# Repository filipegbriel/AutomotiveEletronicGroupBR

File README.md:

# AutomotiveEletronicGroupBR
This is the gitdepository for the academic automotive eletronic group, composed mainly by FATEC and USP.

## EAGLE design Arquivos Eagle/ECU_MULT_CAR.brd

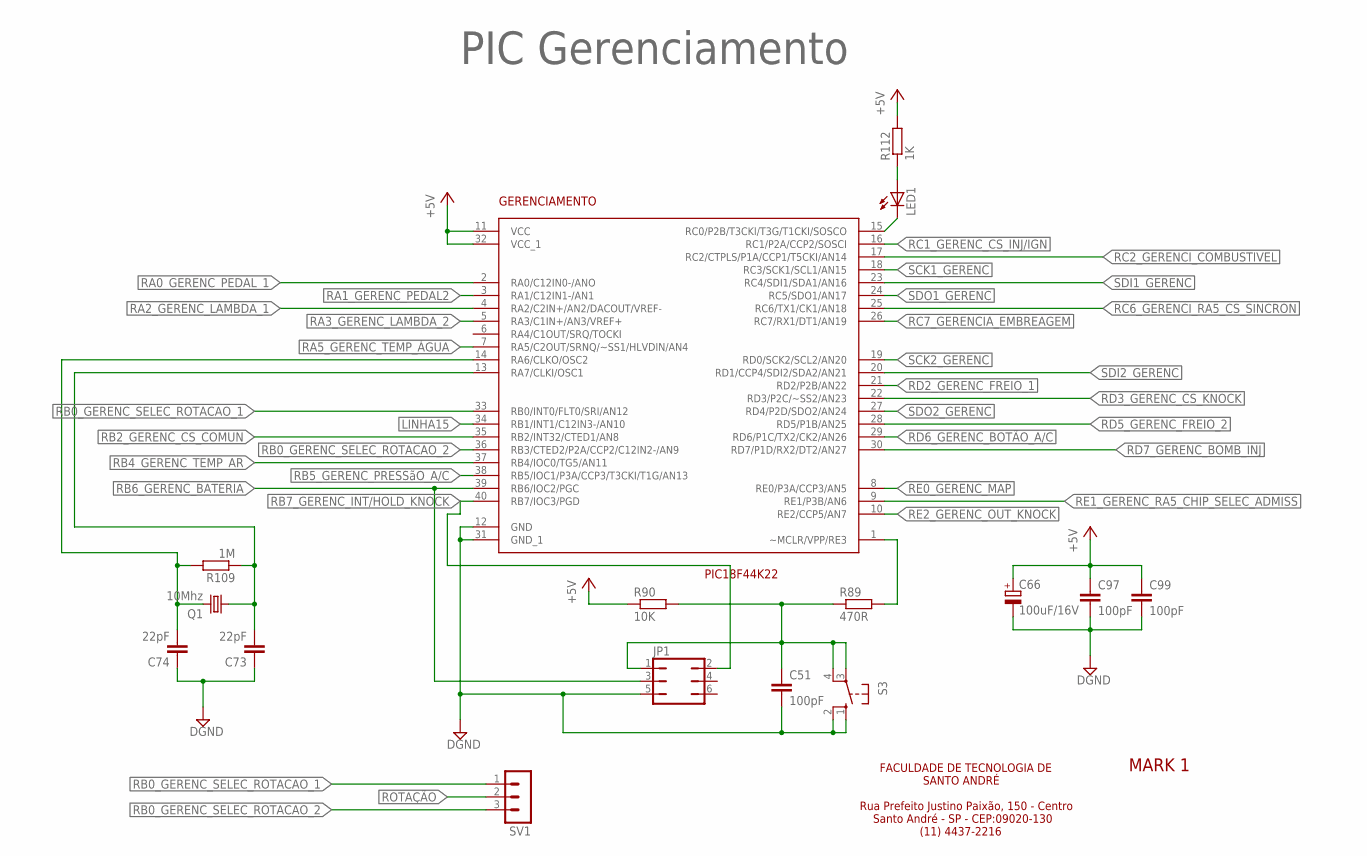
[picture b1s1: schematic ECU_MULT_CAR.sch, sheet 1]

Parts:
C51, C97, C99: 100pF; C0805
C66: 100uF/16V; E2,5-7
C73, C74: 22pF; C0805
GERENCIAMENTO: PIC18F44K22; DIP40
JP1: JP3Q
LED1: LEDKA-3528ASYC; KA-3528ASYC
Q1: 10Mhz; SM49
R89: 470R; M0805
R90: 10K; M0805
R109: 1M; M0805
R112: 1K; M0805
S3: 10-XX; B3F-10XX
SV1: MA03-1

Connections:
+5V: C66.+, C97.1, C99.1, GERENCIAMENTO.11 (VCC), GERENCIAMENTO.32 (VCC_1), R90.1, R112.2; also elsewhere on the board
DGND: C51.2, C66.-, C73.1, C74.1, C97.2, C99.2, GERENCIAMENTO.12 (GND), GERENCIAMENTO.31 (GND_1), JP1.5, S3.1 (S), S3.2 (S1); also elsewhere on the board
LINHA15: GERENCIAMENTO.34 (RB1/INT1/C12IN3-/AN10); also elsewhere on the board
unnamed: C73.2, GERENCIAMENTO.13 (RA7/CLKI/OSC1), Q1.1, R109.1
unnamed: GERENCIAMENTO.1 (~MCLR/VPP/RE3), R89.2
unnamed: C51.1, JP1.1, R89.1, R90.2, S3.3, S3.4 (P1)
unnamed: GERENCIAMENTO.15 (RC0/P2B/T3CKI/T3G/T1CKI/SOSCO), LED1.C
unnamed: LED1.A, R112.1
unnamed: C74.2, GERENCIAMENTO.14 (RA6/CLKO/OSC2), Q1.2, R109.2
RA0_GERENC_PEDAL_1: GERENCIAMENTO.2 (RA0/C12IN0-/ANO); also elsewhere on the board
RA1_GERENC_PEDAL2: GERENCIAMENTO.3 (RA1/C12IN1-/AN1); also elsewhere on the board
RA2_GERENC_LAMBDA_1: GERENCIAMENTO.4 (RA2/C2IN+/AN2/DACOUT/VREF-); also elsewhere on the board
RA3_GERENC_LAMBDA_2: GERENCIAMENTO.5 (RA3/C1IN+/AN3/VREF+); also elsewhere on the board
RA5_GERENC_TEMP_ÁGUA: GERENCIAMENTO.7 (RA5/C2OUT/SRNQ/~SS1/HLVDIN/AN4); also elsewhere on the board
RB0_GERENC_SELEC_ROTACAO_1: GERENCIAMENTO.33 (RB0/INT0/FLT0/SRI/AN12), SV1.1
RB0_GERENC_SELEC_ROTACAO_2: GERENCIAMENTO.36 (RB3/CTED2/P2A/CCP2/C12IN2-/AN9), SV1.3
RB2_GERENC_CS_COMUN: GERENCIAMENTO.35 (RB2/INT32/CTED1/AN8); also elsewhere on the board
RB4_GERENC_TEMP_AR: GERENCIAMENTO.37 (RB4/IOC0/TG5/AN11); also elsewhere on the board
RB5_GERENC_PRESSãO_A/C: GERENCIAMENTO.38 (RB5/IOC1/P3A/CCP3/T3CKI/T1G/AN13); also elsewhere on the board
RB6_GERENC_BATERIA: GERENCIAMENTO.39 (RB6/IOC2/PGC), JP1.3; also elsewhere on the board
RB7_GERENC_INT/HOLD_KNOCK: GERENCIAMENTO.40 (RB7/IOC3/PGD), JP1.2; also elsewhere on the board
RC1_GERENC_CS_INJ/IGN: GERENCIAMENTO.16 (RC1/P2A/CCP2/SOSCI); also elsewhere on the board
RC2_GERENCI_COMBUSTIVEL: GERENCIAMENTO.17 (RC2/CTPLS/P1A/CCP1/T5CKI/AN14); also elsewhere on the board
RC6_GERENCI_RA5_CS_SINCRON: GERENCIAMENTO.25 (RC6/TX1/CK1/AN18); also elsewhere on the board
RC7_GERENCIA_EMBREAGEM: GERENCIAMENTO.26 (RC7/RX1/DT1/AN19); also elsewhere on the board
RD2_GERENC_FREIO_1: GERENCIAMENTO.21 (RD2/P2B/AN22); also elsewhere on the board
RD3_GERENC_CS_KNOCK: GERENCIAMENTO.22 (RD3/P2C/~SS2/AN23); also elsewhere on the board
RD5_GERENC_FREIO_2: GERENCIAMENTO.28 (RD5/P1B/AN25); also elsewhere on the board
RD6_GERENC_BOTÃO_A/C: GERENCIAMENTO.29 (RD6/P1C/TX2/CK2/AN26); also elsewhere on the board
RD7_GERENC_BOMB_INJ: GERENCIAMENTO.30 (RD7/P1D/RX2/DT2/AN27); also elsewhere on the board
RE0_GERENC_MAP: GERENCIAMENTO.8 (RE0/P3A/CCP3/AN5); also elsewhere on the board
RE1_GERENC_RA5_CHIP_SELEC_ADMISS: GERENCIAMENTO.9 (RE1/P3B/AN6); also elsewhere on the board
RE2_GERENC_OUT_KNOCK: GERENCIAMENTO.10 (RE2/CCP5/AN7); also elsewhere on the board
ROTAÇÃO: SV1.2; also elsewhere on the board
SCK1_GERENC: GERENCIAMENTO.18 (RC3/SCK1/SCL1/AN15); also elsewhere on the board
SCK2_GERENC: GERENCIAMENTO.19 (RD0/SCK2/SCL2/AN20); also elsewhere on the board
SDI1_GERENC: GERENCIAMENTO.23 (RC4/SDI1/SDA1/AN16); also elsewhere on the board
SDI2_GERENC: GERENCIAMENTO.20 (RD1/CCP4/SDI2/SDA2/AN21); also elsewhere on the board
SDO1_GERENC: GERENCIAMENTO.24 (RC5/SDO1/AN17); also elsewhere on the board
SDO2_GERENC: GERENCIAMENTO.27 (RD4/P2D/SDO2/AN24); also elsewhere on the board

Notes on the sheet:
PIC Gerenciamento
FACULDADE DE TECNOLOGIA DE SANTO ANDRÉ Rua Prefeito Justino Paixão, 150 - Centro Santo André - SP - CEP:09020-130 (11) 4437-2216
MARK 1

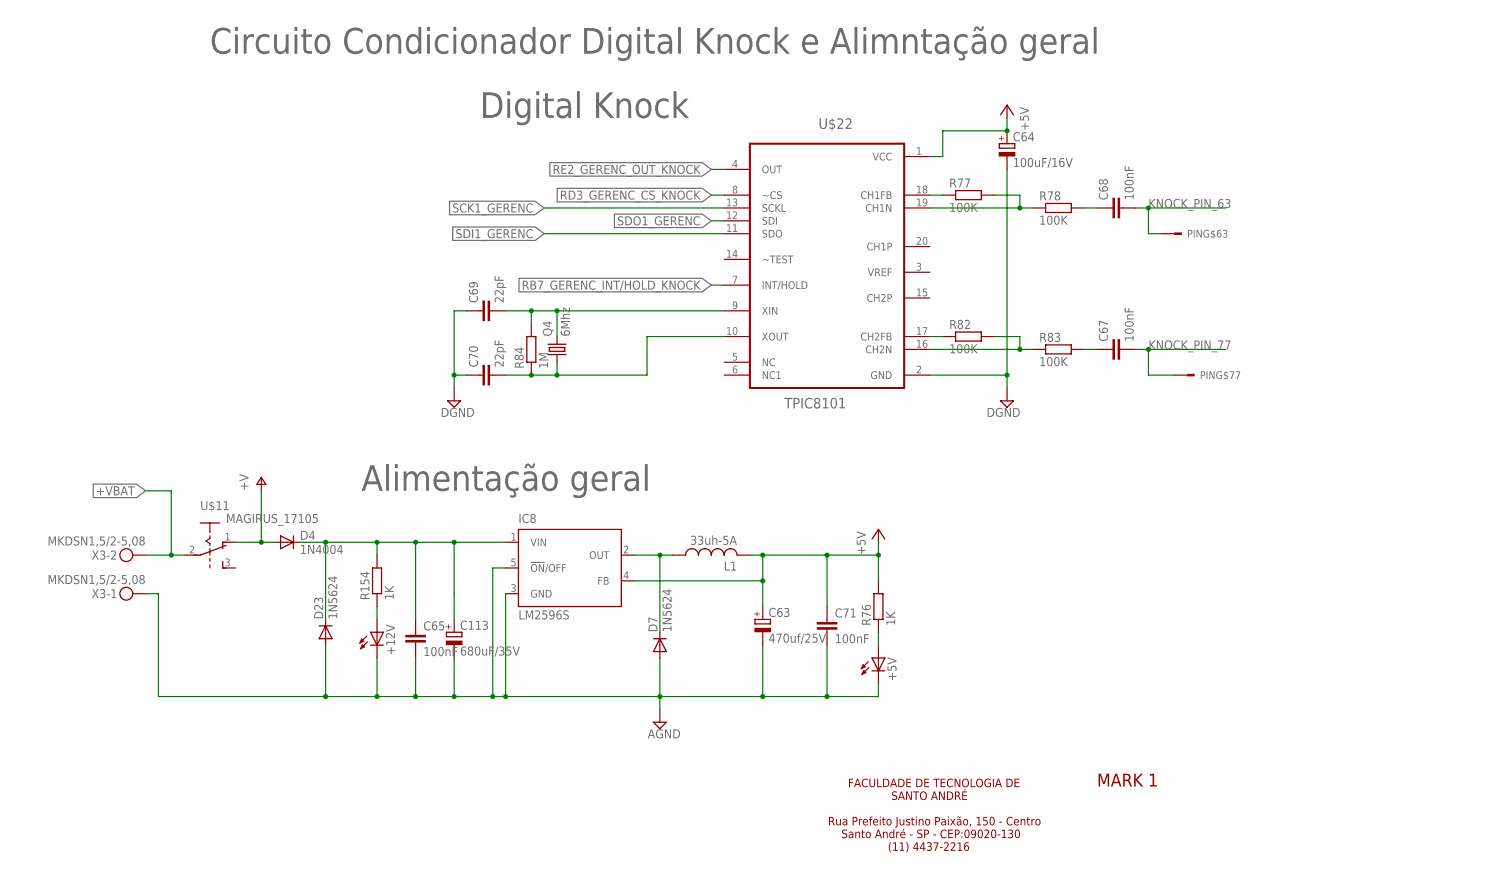
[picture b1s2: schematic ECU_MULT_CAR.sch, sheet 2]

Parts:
+5V, +12V: LEDKA-3528ASYC; KA-3528ASYC
C63: 470uf/25V; E3,5-8
C64: 100uF/16V; E2,5-7
C65, C67, C68, C71: 100nF; C0805
C69, C70: 22pF; C0805
C113: 680uF/35V; E3,5-10
D4: 1N4004; DO41-10
D7, D23: 1N5624; DO201-15
IC8: LM2596S; TO263-5
L1: 33uh-5A; POWER-CHOKE_WE-TPC
PIN: CONCTOR_BOSCH; V23542-A1280-B300
Q4: 6Mhz; SM49
R76, R154: 1K; M0805
R77, R78, R82, R83: 100K; M0805
R84: 1M; M0805
U$11: MAGIRUS_17105; MAGIRUS_TICTAC_3_PIN
U$22: TPIC8101; SOIC-20P
X3: MKDSN1,5/2-5,08

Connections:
+5V: C63.+, C64.+, C71.1, IC8.4 (FB), L1.2, R76.2, U$22.1 (VCC); also elsewhere on the board
+VBAT: U$11.2, X3.2; also elsewhere on the board
DGND: C64.-, C69.1, C70.1, U$22.2 (GND); also elsewhere on the board
GND3: +5V.C, +12V.C, C63.-, C65.2, C71.2, C113.-, D7.A, D23.A, IC8.3 (GND), IC8.5 (!ON!/OFF), X3.1; also elsewhere on the board
KNOCK_PIN_63: C68.2, PIN.63
KNOCK_PIN_77: C67.2, PIN.77
unnamed: R82.1, U$22.17 (CH2FB)
unnamed: +12V.A, R154.1
unnamed: C65.1, C113.+, D4.C, D23.C, IC8.1 (VIN), R154.2
unnamed: D7.C, IC8.2 (OUT), L1.1
unnamed: R77.1, U$22.18 (CH1FB)
unnamed: R77.2, R78.1, U$22.19 (CH1N)
unnamed: +5V.A, R76.1
unnamed: C68.1, R78.2
unnamed: R82.2, R83.1, U$22.16 (CH2N)
unnamed: C67.1, R83.2
unnamed: C70.2, Q4.1, R84.1, U$22.10 (XOUT)
unnamed: C69.2, Q4.2, R84.2, U$22.9 (XIN)
RB7_GERENC_INT/HOLD_KNOCK: U$22.7 (INT/HOLD); also elsewhere on the board
RD3_GERENC_CS_KNOCK: U$22.8 (~CS); also elsewhere on the board
RE2_GERENC_OUT_KNOCK: U$22.4 (OUT); also elsewhere on the board
SCK1_GERENC: U$22.13 (SCKL); also elsewhere on the board
SDI1_GERENC: U$22.11 (SDO); also elsewhere on the board
SDO1_GERENC: U$22.12 (SDI); also elsewhere on the board
V+: D4.A, U$11.1; also elsewhere on the board

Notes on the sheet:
Digital Knock
Alimentação geral
Circuito Condicionador Digital Knock e Alimntação geral
FACULDADE DE TECNOLOGIA DE SANTO ANDRÉ Rua Prefeito Justino Paixão, 150 - Centro Santo André - SP - CEP:09020-130 (11) 4437-2216
MARK 1

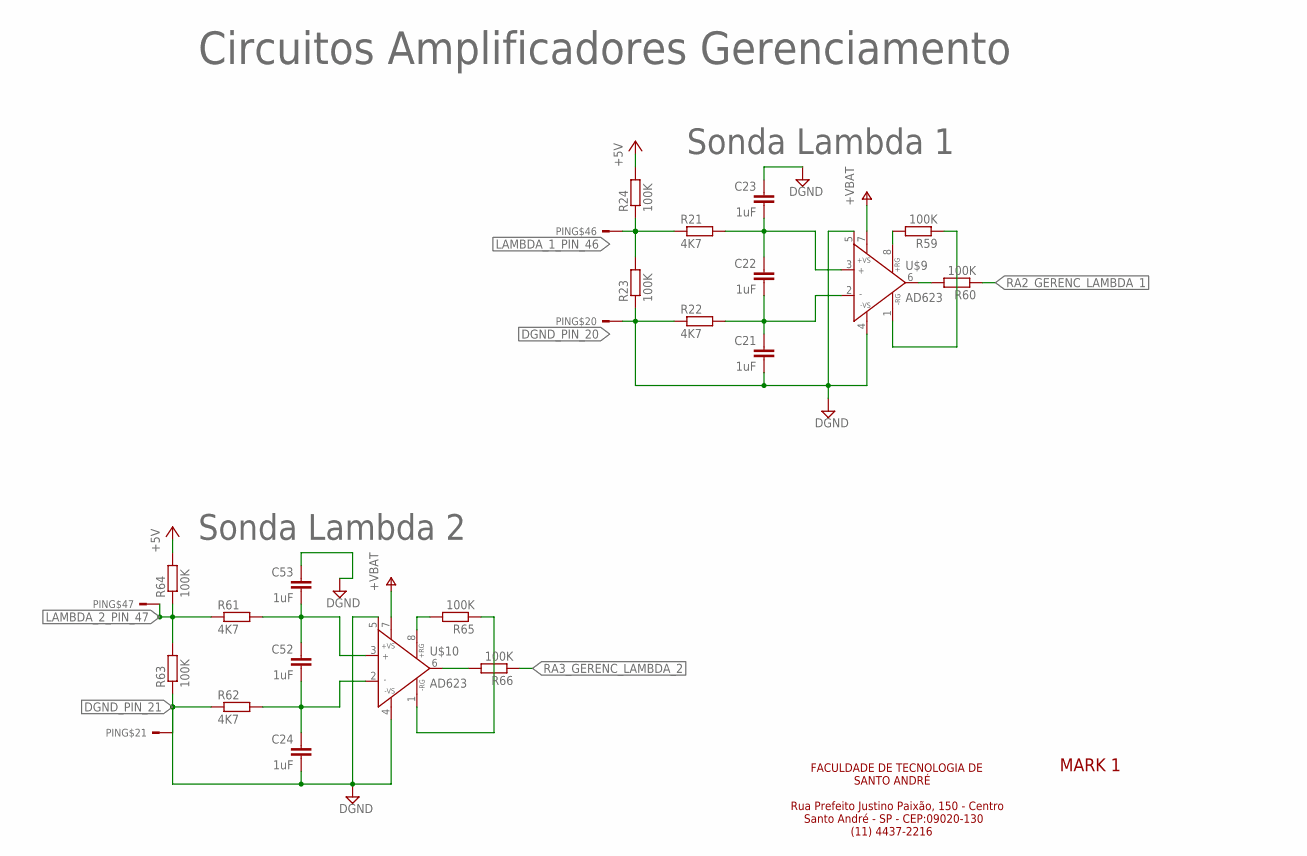
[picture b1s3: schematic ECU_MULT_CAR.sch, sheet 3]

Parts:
C21, C22, C23, C24, C52, C53: 1uF; C0805
PIN: CONCTOR_BOSCH; V23542-A1280-B300
R21, R22, R61, R62: 4K7; M0805
R23, R24, R59, R60, R63, R64, R65, R66: 100K; M0805
U$9, U$10: AD623; SOIC-8

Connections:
+5V: R24.2, R64.2; also elsewhere on the board
DGND: C23.1, C53.1; also elsewhere on the board
DGND_PIN_20: C21.2, PIN.20, R22.1, R23.1, U$9.4 (-VS), U$9.5 (REF)
DGND_PIN_21: C24.2, PIN.21, R62.1, R63.1, U$10.4 (-VS), U$10.5 (REF)
LAMBDA_1_PIN_46: PIN.46, R21.1, R23.2, R24.1
LAMBDA_2_PIN_47: PIN.47, R61.1, R63.2, R64.1
unnamed: C22.1, C23.2, R21.2, U$9.3 (+IN)
unnamed: C21.1, C22.2, R22.2, U$9.2 (-IN)
unnamed: C52.1, C53.2, R61.2, U$10.3 (+IN)
unnamed: C24.1, C52.2, R62.2, U$10.2 (-IN)
unnamed: R59.2, U$9.8 (+RG)
unnamed: R59.1, U$9.1 (-RG)
unnamed: R60.2, U$9.6 (OUTPUT)
unnamed: R65.2, U$10.8 (+RG)
unnamed: R65.1, U$10.1 (-RG)
unnamed: R66.2, U$10.6 (OUTPUT)
RA2_GERENC_LAMBDA_1: R60.1; also elsewhere on the board
RA3_GERENC_LAMBDA_2: R66.1; also elsewhere on the board
V+: U$9.7 (+VS), U$10.7 (+VS); also elsewhere on the board

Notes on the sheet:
Sonda Lambda 1
Sonda Lambda 2
Circuitos Amplificadores Gerenciamento
FACULDADE DE TECNOLOGIA DE SANTO ANDRÉ Rua Prefeito Justino Paixão, 150 - Centro Santo André - SP - CEP:09020-130 (11) 4437-2216
MARK 1

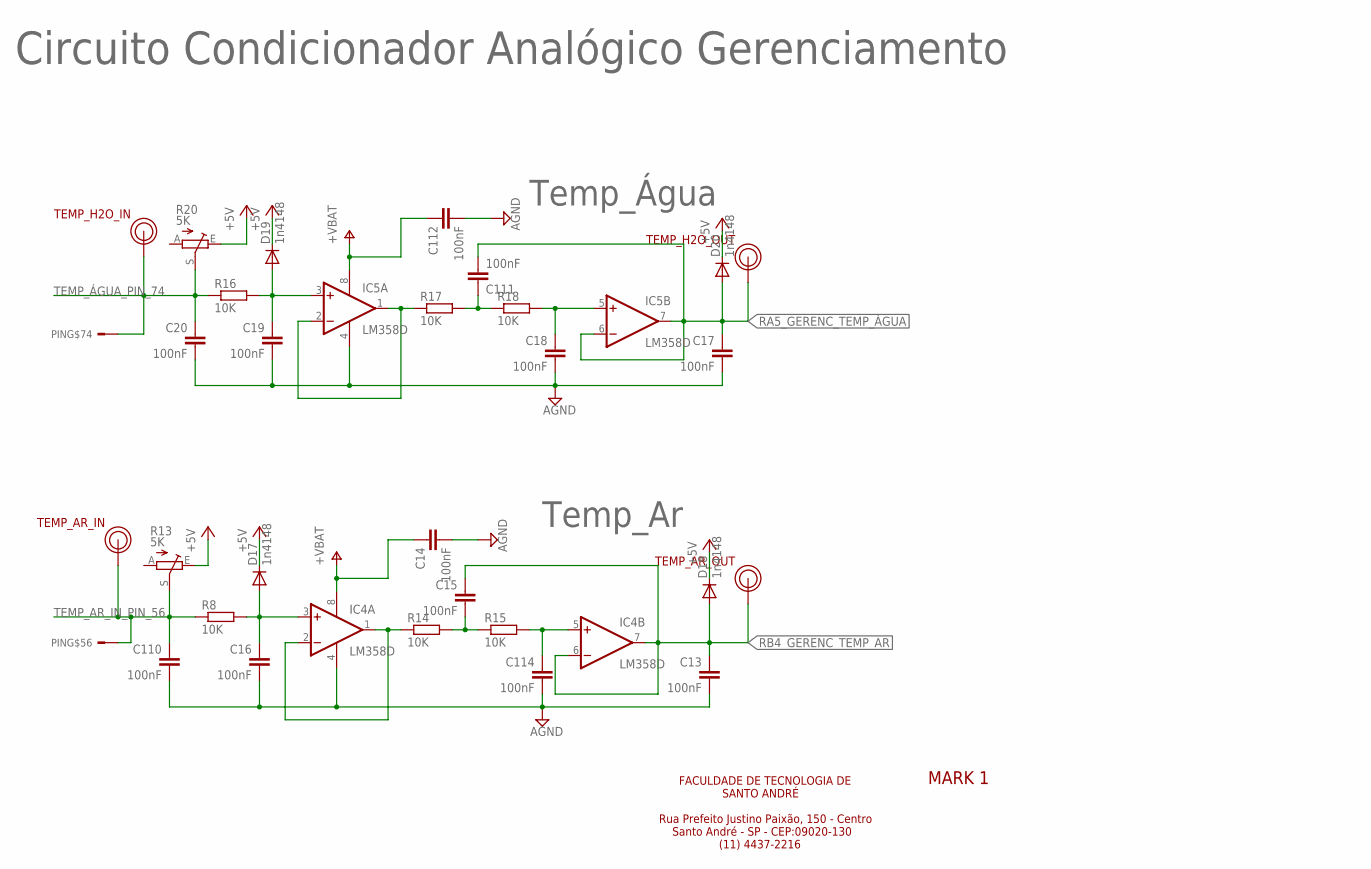
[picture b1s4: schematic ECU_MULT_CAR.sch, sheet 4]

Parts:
C13, C14, C15, C16, C17, C18, C19, C20, C110, C111, C112, C114: 100nF; C0805
D17, D18, D19, D20: 1n4148; MINIMELF
IC4, IC5: LM358D; SO08
PIN: CONCTOR_BOSCH; V23542-A1280-B300
R8, R14, R15, R16, R17, R18: 10K; M0805
R13, R20: 5K; S63P
TEMP_AR_IN: PINO_TORNEADO
TEMP_AR_OUT: PINO_TORNEADO
TEMP_H2O_IN, TEMP_H2O_OUT: PINO_TORNEADO

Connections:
+5V: D17.C, D18.C, D19.C, D20.C, R13.E, R20.E; also elsewhere on the board
GND3: C13.2, C14.2, C16.2, C17.2, C18.2, C19.2, C20.2, C110.2, C112.2, C114.2, IC4.4 (V-), IC5.4 (V-); also elsewhere on the board
unnamed: C16.1, D17.A, IC4.3 (+IN), R8.2
unnamed: C19.1, D19.A, IC5.3 (+IN), R16.2
unnamed: IC4.1 (OUT), IC4.2 (-IN), R14.1
unnamed: C15.2, R14.2, R15.1
unnamed: C114.1, IC4.5 (+IN), R15.2
unnamed: IC5.1 (OUT), IC5.2 (-IN), R17.1
unnamed: C111.1, R17.2, R18.1
unnamed: C18.1, IC5.5 (+IN), R18.2
RA5_GERENC_TEMP_ÁGUA: C17.1, C111.2, D20.A, IC5.6 (-IN), IC5.7 (OUT), TEMP_H2O_OUT.1; also elsewhere on the board
RB4_GERENC_TEMP_AR: C13.1, C15.1, D18.A, IC4.6 (-IN), IC4.7 (OUT), TEMP_AR_OUT.1; also elsewhere on the board
TEMP_AR_IN_PIN_56: C110.1, PIN.56, R8.1, R13.S, TEMP_AR_IN.1
TEMP_ÁGUA_PIN_74: C20.1, PIN.74, R16.1, R20.S, TEMP_H2O_IN.1
V+: C14.1, C112.1, IC4.8 (V+), IC5.8 (V+); also elsewhere on the board

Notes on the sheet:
Temp_Ar
Temp_Água
Circuito Condicionador Analógico Gerenciamento
FACULDADE DE TECNOLOGIA DE SANTO ANDRÉ Rua Prefeito Justino Paixão, 150 - Centro Santo André - SP - CEP:09020-130 (11) 4437-2216
MARK 1

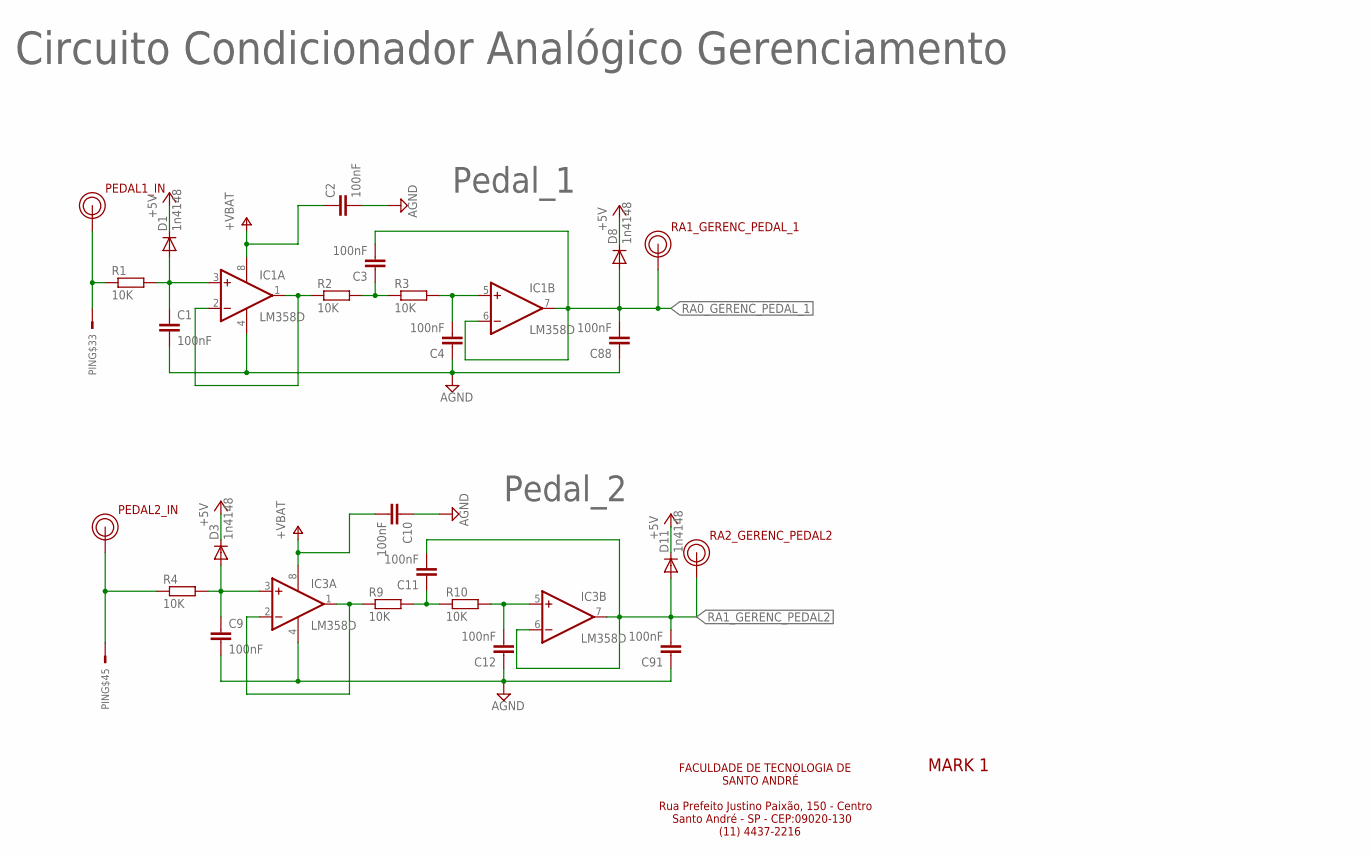
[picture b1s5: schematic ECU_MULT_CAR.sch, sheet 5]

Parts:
C1, C2, C3, C4, C9, C10, C11, C12, C88, C91: 100nF; C0805
D1, D3, D8, D11: 1n4148; MINIMELF
IC1, IC3: LM358D; SO08
PEDAL1_IN, PEDAL2_IN: PINO_TORNEADO
PIN: CONCTOR_BOSCH; V23542-A1280-B300
R1, R2, R3, R4, R9, R10: 10K; M0805
RA1_GERENC_PEDAL_1, RA2_GERENC_PEDAL2: PINO_TORNEADO

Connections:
+5V: D1.C, D3.C, D8.C, D11.C; also elsewhere on the board
GND3: C1.2, C2.2, C4.1, C9.2, C10.1, C12.1, C88.1, C91.1, IC1.4 (V-), IC3.4 (V-); also elsewhere on the board
unnamed: C1.1, D1.A, IC1.3 (+IN), R1.2
unnamed: IC1.1 (OUT), IC1.2 (-IN), R2.1
unnamed: C9.1, D3.A, IC3.3 (+IN), R4.2
unnamed: C3.1, R2.2, R3.1
unnamed: C4.2, IC1.5 (+IN), R3.2
unnamed: IC3.1 (OUT), IC3.2 (-IN), R9.1
unnamed: C11.1, R9.2, R10.1
unnamed: C12.2, IC3.5 (+IN), R10.2
PEDAL1_PIN_33: PEDAL1_IN.1, PIN.33, R1.1
PEDAL2_PIN_45: PEDAL2_IN.1, PIN.45, R4.1
RA0_GERENC_PEDAL_1: C3.2, C88.2, D8.A, IC1.6 (-IN), IC1.7 (OUT), RA1_GERENC_PEDAL_1.1; also elsewhere on the board
RA1_GERENC_PEDAL2: C11.2, C91.2, D11.A, IC3.6 (-IN), IC3.7 (OUT), RA2_GERENC_PEDAL2.1; also elsewhere on the board
V+: C2.1, C10.2, IC1.8 (V+), IC3.8 (V+); also elsewhere on the board

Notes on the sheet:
Pedal_1
Pedal_2
Circuito Condicionador Analógico Gerenciamento
FACULDADE DE TECNOLOGIA DE SANTO ANDRÉ Rua Prefeito Justino Paixão, 150 - Centro Santo André - SP - CEP:09020-130 (11) 4437-2216
MARK 1

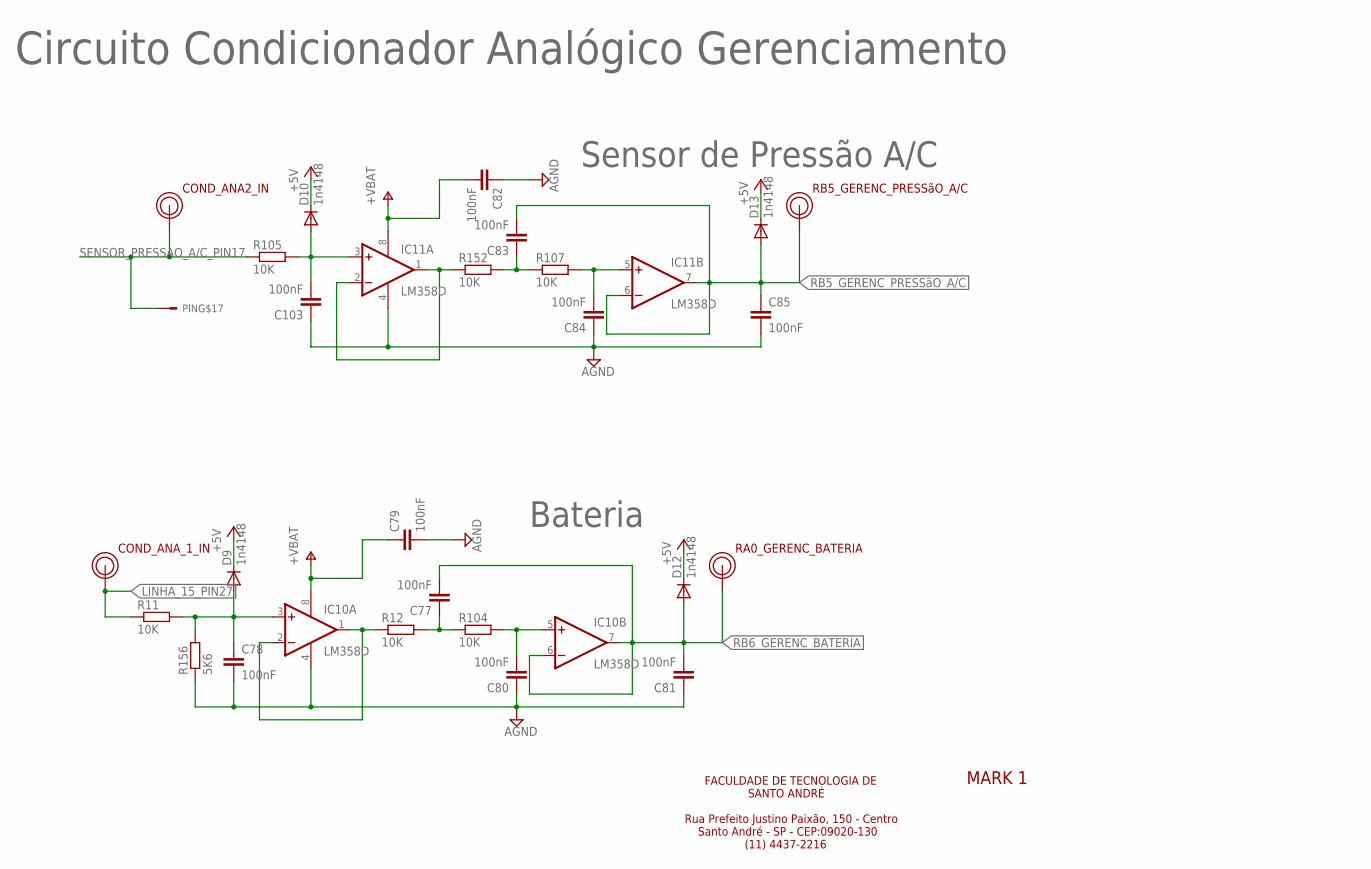
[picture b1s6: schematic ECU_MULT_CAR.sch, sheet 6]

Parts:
C77, C78, C79, C80, C81, C82, C83, C84, C85, C103: 100nF; C0805
COND_ANA2_IN: PINO_TORNEADO
COND_ANA_1_IN: PINO_TORNEADO
D9, D10, D12, D13: 1n4148; MINIMELF
IC10, IC11: LM358D; SO08
PIN: CONCTOR_BOSCH; V23542-A1280-B300
R11, R12, R104, R105, R107, R152: 10K; M0805
R156: 5K6; M0805
RA0_GERENC_BATERIA: PINO_TORNEADO
RB5_GERENC_PRESSãO_A/C: PINO_TORNEADO

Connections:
+5V: D9.C, D10.C, D12.C, D13.C; also elsewhere on the board
GND3: C78.2, C79.2, C80.1, C81.1, C82.1, C84.1, C85.2, C103.1, IC10.4 (V-), IC11.4 (V-), R156.1; also elsewhere on the board
LINHA_15_PIN27: COND_ANA_1_IN.1, R11.1; also elsewhere on the board
unnamed: C78.1, D9.A, IC10.3 (+IN), R11.2, R156.2
unnamed: IC10.1 (OUT), IC10.2 (-IN), R12.1
unnamed: C77.1, R12.2, R104.1
unnamed: C80.2, IC10.5 (+IN), R104.2
unnamed: C103.2, D10.A, IC11.3 (+IN), R105.2
unnamed: IC11.1 (OUT), IC11.2 (-IN), R152.1
unnamed: C83.1, R107.1, R152.2
unnamed: C84.2, IC11.5 (+IN), R107.2
RB5_GERENC_PRESSãO_A/C: C83.2, C85.1, D13.A, IC11.6 (-IN), IC11.7 (OUT), RB5_GERENC_PRESSãO_A/C.1; also elsewhere on the board
RB6_GERENC_BATERIA: C77.2, C81.2, D12.A, IC10.6 (-IN), IC10.7 (OUT), RA0_GERENC_BATERIA.1; also elsewhere on the board
SENSOR_PRESSAO_A/C_PIN17: COND_ANA2_IN.1, PIN.17, R105.1
V+: C79.1, C82.2, IC10.8 (V+), IC11.8 (V+); also elsewhere on the board

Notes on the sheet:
Bateria
Circuito Condicionador Analógico Gerenciamento
Sensor de Pressão A/C
FACULDADE DE TECNOLOGIA DE SANTO ANDRÉ Rua Prefeito Justino Paixão, 150 - Centro Santo André - SP - CEP:09020-130 (11) 4437-2216
MARK 1

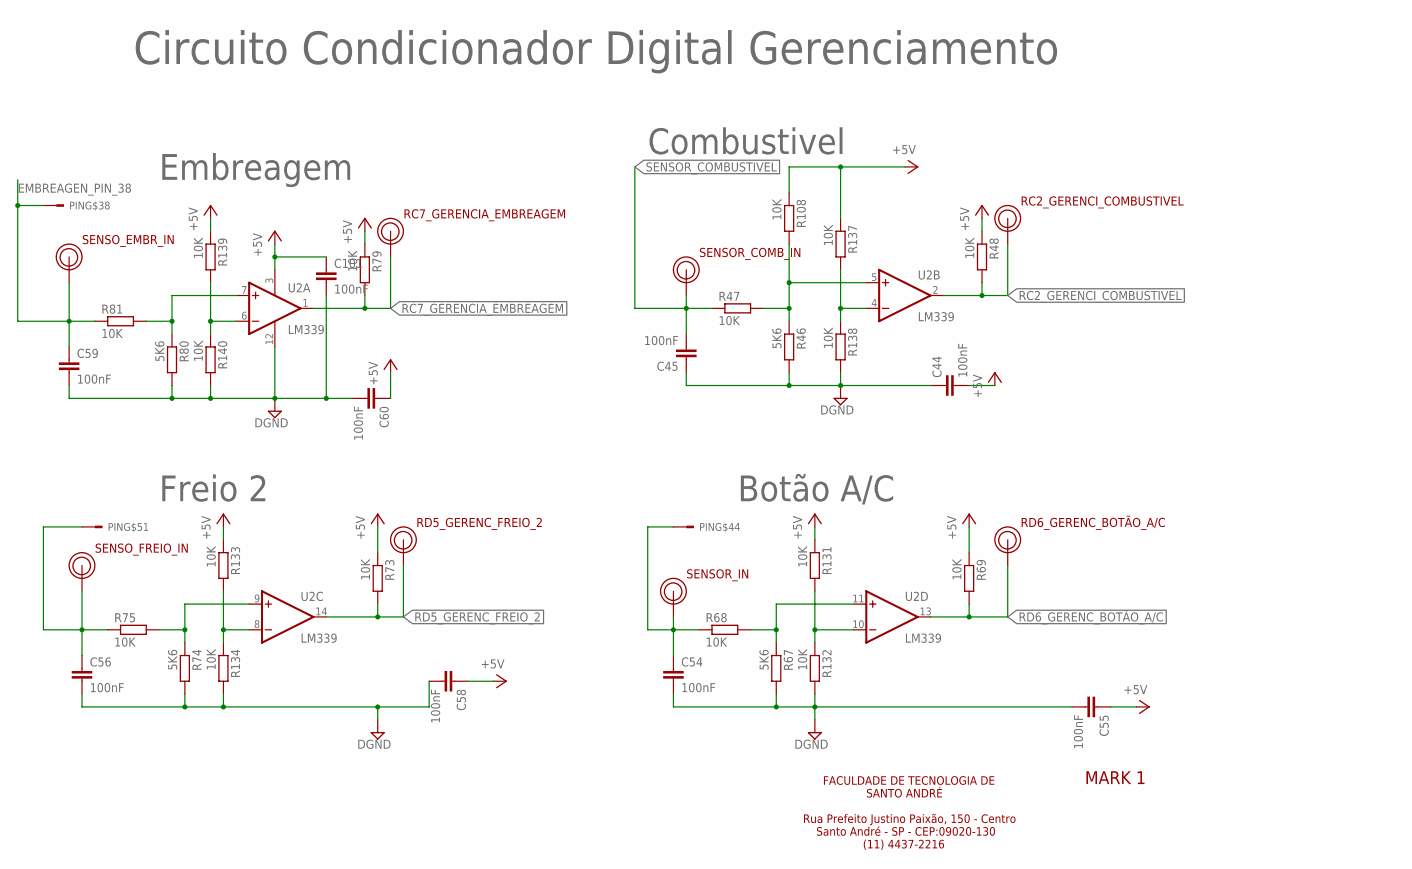
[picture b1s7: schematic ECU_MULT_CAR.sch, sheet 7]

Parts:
C44, C45, C54, C55, C56, C58, C59, C60, C101: 100nF; C0805
PIN: CONCTOR_BOSCH; V23542-A1280-B300
R46, R67, R74, R80: 5K6; M0805
R47, R48, R68, R69, R73, R75, R79, R81, R108, R131, R132, R133, R134, R137, R138, R139, R140: 10K; M0805
RC2_GERENCI_COMBUSTIVEL, RC7_GERENCIA_EMBREAGEM: PINO_TORNEADO
RD5_GERENC_FREIO_2, RD6_GERENC_BOTÃO_A/C: PINO_TORNEADO
SENSOR_COMB_IN: PINO_TORNEADO
SENSOR_IN: PINO_TORNEADO
SENSO_EMBR_IN: PINO_TORNEADO
SENSO_FREIO_IN: PINO_TORNEADO
U2: LM339; SOIC14N

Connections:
+5V: C44.2, C55.1, C58.1, C60.1, C101.1, R48.1, R69.1, R73.1, R79.1, R108.1, R131.1, R133.1, R137.1, R139.1, U2.3 (V+); also elsewhere on the board
BOTAO_A/C_ACION_AR_COND_PIN44: C54.1, PIN.44, R68.1, SENSOR_IN.1
DGND: C44.1, C45.1, C54.2, C55.2, C56.2, C58.2, C59.2, C60.2, C101.2, R46.2, R67.2, R74.2, R80.2, R132.2, R134.2, R138.2, R140.2, U2.12 (V-); also elsewhere on the board
EMBREAGEN_PIN_38: C59.1, PIN.38, R81.1, SENSO_EMBR_IN.1
FREIO_PIN_51: C56.1, PIN.51, R75.1, SENSO_FREIO_IN.1
unnamed: R46.1, R47.2, R108.2, U2.5 (+IN)
unnamed: R67.1, R68.2, U2.11 (+IN)
unnamed: R74.1, R75.2, U2.9 (+IN)
unnamed: R80.1, R81.2, U2.7 (+IN)
unnamed: R131.2, R132.1, U2.10 (-IN)
unnamed: R137.2, R138.1, U2.4 (-IN)
unnamed: R133.2, R134.1, U2.8 (-IN)
unnamed: R139.2, R140.1, U2.6 (-IN)
RC2_GERENCI_COMBUSTIVEL: R48.2, RC2_GERENCI_COMBUSTIVEL.1, U2.2 (OUT); also elsewhere on the board
RC7_GERENCIA_EMBREAGEM: R79.2, RC7_GERENCIA_EMBREAGEM.1, U2.1 (OUT); also elsewhere on the board
RD5_GERENC_FREIO_2: R73.2, RD5_GERENC_FREIO_2.1, U2.14 (OUT); also elsewhere on the board
RD6_GERENC_BOTÃO_A/C: R69.2, RD6_GERENC_BOTÃO_A/C.1, U2.13 (OUT); also elsewhere on the board
SENSOR_COMBUSTIVEL: C45.2, R47.1, SENSOR_COMB_IN.1; also elsewhere on the board

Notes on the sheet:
Combustivel
Botão A/C
Embreagem
Freio 2
Circuito Condicionador Digital Gerenciamento
FACULDADE DE TECNOLOGIA DE SANTO ANDRÉ Rua Prefeito Justino Paixão, 150 - Centro Santo André - SP - CEP:09020-130 (11) 4437-2216
MARK 1

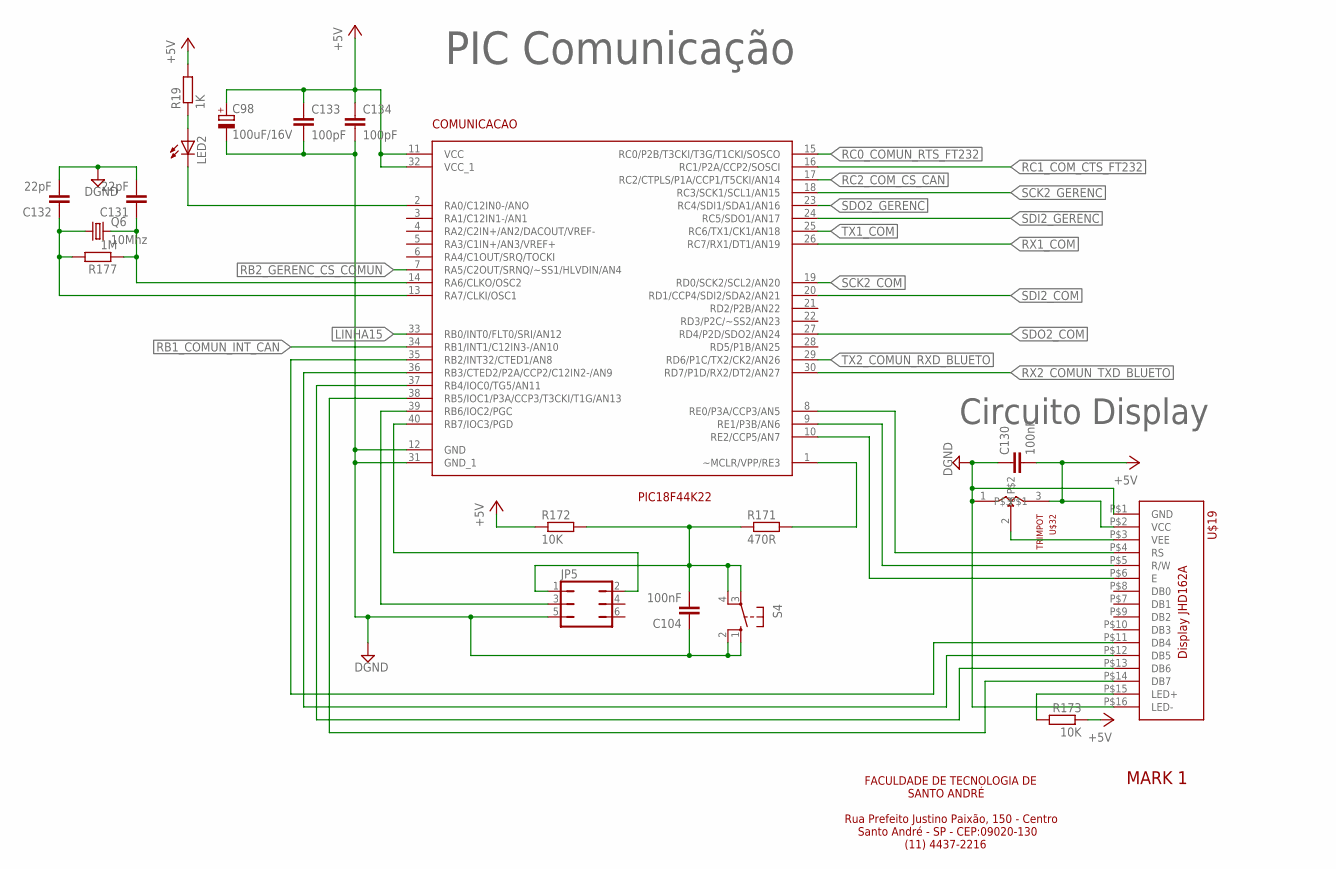
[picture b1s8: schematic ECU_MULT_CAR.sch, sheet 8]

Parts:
C98: 100uF/16V; E2,5-7
C104, C130: 100nF; C0805
C131, C132: 22pF; C0805
C133, C134: 100pF; C0805
COMUNICACAO: PIC18F44K22; DIP40
JP5: JP3Q
LED2: LEDKA-3528ASYC; KA-3528ASYC
Q6: 10Mhz; SM49
R19: 1K; M0805
R171: 470R; M0805
R172, R173: 10K; M0805
R177: 1M; M0805
S4: 10-XX; B3F-10XX
U$19: JHD162A
U$32: TRIMPOT

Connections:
+5V: C98.+, C130.2, C133.1, C134.1, COMUNICACAO.11 (VCC), COMUNICACAO.32 (VCC_1), R19.2, R172.1, R173.1, U$19.P$2 (VCC), U$32.3; also elsewhere on the board
DGND: C98.-, C104.1, C130.1, C131.2, C132.2, C133.2, C134.2, COMUNICACAO.12 (GND), COMUNICACAO.31 (GND_1), JP5.5, S4.1 (S), S4.2 (S1), U$19.P$1 (GND), U$19.P$16 (LED-), U$32.1; also elsewhere on the board
LINHA15: COMUNICACAO.33 (RB0/INT0/FLT0/SRI/AN12); also elsewhere on the board
unnamed: COMUNICACAO.2 (RA0/C12IN0-/ANO), LED2.C
unnamed: LED2.A, R19.1
unnamed: COMUNICACAO.38 (RB5/IOC1/P3A/CCP3/T3CKI/T1G/AN13), U$19.P$14 (DB7)
unnamed: COMUNICACAO.37 (RB4/IOC0/TG5/AN11), U$19.P$13 (DB6)
unnamed: COMUNICACAO.36 (RB3/CTED2/P2A/CCP2/C12IN2-/AN9), U$19.P$12 (DB5)
unnamed: COMUNICACAO.35 (RB2/INT32/CTED1/AN8), U$19.P$11 (DB4)
unnamed: C104.2, JP5.1, R171.1, R172.2, S4.3, S4.4 (P1)
unnamed: COMUNICACAO.40 (RB7/IOC3/PGD), JP5.2
unnamed: COMUNICACAO.1 (~MCLR/VPP/RE3), R171.2
unnamed: C131.1, COMUNICACAO.14 (RA6/CLKO/OSC2), Q6.2, R177.1
unnamed: R173.2, U$19.P$15 (LED+)
unnamed: U$19.P$3 (VEE), U$32.2
unnamed: C132.1, COMUNICACAO.13 (RA7/CLKI/OSC1), Q6.1, R177.2
unnamed: COMUNICACAO.39 (RB6/IOC2/PGC), JP5.3
unnamed: COMUNICACAO.8 (RE0/P3A/CCP3/AN5), U$19.P$4 (RS)
unnamed: COMUNICACAO.9 (RE1/P3B/AN6), U$19.P$5 (R/W)
unnamed: COMUNICACAO.10 (RE2/CCP5/AN7), U$19.P$6 (E)
RB1_COMUN_INT_CAN: COMUNICACAO.34 (RB1/INT1/C12IN3-/AN10); also elsewhere on the board
RB2_GERENC_CS_COMUN: COMUNICACAO.7 (RA5/C2OUT/SRNQ/~SS1/HLVDIN/AN4); also elsewhere on the board
RC0_COMUN_RTS_FT232: COMUNICACAO.15 (RC0/P2B/T3CKI/T3G/T1CKI/SOSCO); also elsewhere on the board
RC1_COM_CTS_FT232: COMUNICACAO.16 (RC1/P2A/CCP2/SOSCI); also elsewhere on the board
RC2_COM_CS_CAN: COMUNICACAO.17 (RC2/CTPLS/P1A/CCP1/T5CKI/AN14); also elsewhere on the board
RX1_COM: COMUNICACAO.26 (RC7/RX1/DT1/AN19); also elsewhere on the board
RX2_COMUN_TXD_BLUETO: COMUNICACAO.30 (RD7/P1D/RX2/DT2/AN27); also elsewhere on the board
SCK2_COM: COMUNICACAO.19 (RD0/SCK2/SCL2/AN20); also elsewhere on the board
SCK2_GERENC: COMUNICACAO.18 (RC3/SCK1/SCL1/AN15); also elsewhere on the board
SDI2_COM: COMUNICACAO.20 (RD1/CCP4/SDI2/SDA2/AN21); also elsewhere on the board
SDI2_GERENC: COMUNICACAO.24 (RC5/SDO1/AN17); also elsewhere on the board
SDO2_COM: COMUNICACAO.27 (RD4/P2D/SDO2/AN24); also elsewhere on the board
SDO2_GERENC: COMUNICACAO.23 (RC4/SDI1/SDA1/AN16); also elsewhere on the board
TX1_COM: COMUNICACAO.25 (RC6/TX1/CK1/AN18); also elsewhere on the board
TX2_COMUN_RXD_BLUETO: COMUNICACAO.29 (RD6/P1C/TX2/CK2/AN26); also elsewhere on the board

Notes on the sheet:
Circuito Display
PIC Comunicação
FACULDADE DE TECNOLOGIA DE SANTO ANDRÉ Rua Prefeito Justino Paixão, 150 - Centro Santo André - SP - CEP:09020-130 (11) 4437-2216
MARK 1

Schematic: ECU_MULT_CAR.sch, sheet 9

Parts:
C125, C126: 100nF; C0805
C127, C128: 10pF; C0805
PIN: CONCTOR_BOSCH; V23542-A1280-B300
Q7: 20MHZ; SM49
R165: 10R; M0805
R166: 120R; M0805
R167, R168: 1K; M0805
R169: 10K; M0805
RXCAN: LEDKA-3528ASYC; KA-3528ASYC
TXCAN: LEDKA-3528ASYC; KA-3528ASYC
U20: PCA82C251T/N3; SOIC127P600X175-8N
U$31: MCP2515-I/SO; SOIC127P1034X264-18N

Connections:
+5V: C125.1, C126.1, R169.2, RXCAN.A, TXCAN.A, U20.3 (VCC), U$31.18 (VDD); also elsewhere on the board
CANH_P: PIN.31, R166.2, U20.7 (CANH)
CANL_N: PIN.32, R166.1, U20.6 (CANL)
DGND: C125.2, C126.2, C127.2, C128.2, R165.1, U20.2 (GND), U$31.9 (VSS); also elsewhere on the board
unnamed: R165.2, U20.8 (RS)
unnamed: R167.2, TXCAN.C
unnamed: R168.2, RXCAN.C
unnamed: R168.1, U20.1 (TXD), U$31.1 (TXCAN)
unnamed: R167.1, U20.4 (RXD), U$31.2 (RXCAN)
unnamed: C127.1, Q7.2, U$31.8 (OSC1)
unnamed: C128.1, Q7.1, U$31.7 (OSC2)
unnamed: R169.1, U$31.17 (~RESET)
RB1_COMUN_INT_CAN: U$31.12 (~INT); also elsewhere on the board
RC2_COM_CS_CAN: U$31.16 (~CS); also elsewhere on the board
SCK2_COM: U$31.13 (SCK); also elsewhere on the board
SDI2_COM: U$31.15 (SO); also elsewhere on the board
SDO2_COM: U$31.14 (SI); also elsewhere on the board

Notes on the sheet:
Circuitos Comunicação
Rede CAN
FACULDADE DE TECNOLOGIA DE SANTO ANDRÉ Rua Prefeito Justino Paixão, 150 - Centro Santo André - SP - CEP:09020-130 (11) 4437-2216
MARK 1

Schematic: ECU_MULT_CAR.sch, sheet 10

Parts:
C119: 4u7F/16V; E2,5-7
C123, C124: 100nF; C0805
IC12: FT232RL; SSOP28
R118, R162: 1K; M0805
R163: 10K; M0805
R164: 4K7; M0805
RX: LEDKA-3528ASYC; KA-3528ASYC
TX: LEDKA-3528ASYC; KA-3528ASYC
U$33: HC-06; FE06
X2: MINI-USB-32005-201; 32005-201

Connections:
+5V: C119.+, C123.1, IC12.4 (VCCIO), IC12.20 (VCC), RX.A, TX.A, U$33.2 (VCC); also elsewhere on the board
DGND: C119.-, C123.2, C124.2, IC12.7 (GND), IC12.18 (GND), IC12.21 (GND), IC12.25 (GND), IC12.26 (TEST), R163.1, U$33.3 (GND), X2.4, X2.5; also elsewhere on the board
unnamed: IC12.16 (USBDM), X2.2
unnamed: IC12.15 (USBDP), X2.3
unnamed: C124.1, IC12.17 (3V3OUT)
unnamed: R118.2, RX.C
unnamed: IC12.23 (CBUS0), R118.1
unnamed: R162.2, TX.C
unnamed: IC12.22 (CBUS1), R162.1
unnamed: IC12.19 (!RESET), R163.2, R164.2
unnamed: R164.1, X2.1
RC0_COMUN_RTS_FT232: IC12.3 (!RTS); also elsewhere on the board
RC1_COM_CTS_FT232: IC12.11 (!CTS); also elsewhere on the board
RX1_COM: IC12.1 (TXD); also elsewhere on the board
RX2_COMUN_TXD_BLUETO: U$33.4 (TXD); also elsewhere on the board
TX1_COM: IC12.5 (RXD); also elsewhere on the board
TX2_COMUN_RXD_BLUETO: U$33.5 (RXD); also elsewhere on the board

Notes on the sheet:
Circuitos Comunicação
Comunicação USB
Modulo Bluetooth
FACULDADE DE TECNOLOGIA DE SANTO ANDRÉ Rua Prefeito Justino Paixão, 150 - Centro Santo André - SP - CEP:09020-130 (11) 4437-2216
MARK 1

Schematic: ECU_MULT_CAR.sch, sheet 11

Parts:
ADMISSÃO: PIC18F44K22; DIP40
C86, C87: 22pF; C0805
C94, C96, C102: 100pF; C0805
C122: 100uF/16V; E2,5-7
JP2: JP3Q
LED16: LEDKA-3528ASYC; KA-3528ASYC
Q2: 10Mhz; SM49
R113: 470R; M0805
R114: 10K; M0805
R115: 1K; M0805
R174: 1M; M0805
S5: 10-XX; B3F-10XX

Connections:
+5V: ADMISSÃO.11 (VCC), ADMISSÃO.32 (VCC_1), C94.1, C96.1, C122.+, R114.1, R115.2; also elsewhere on the board
DGND: ADMISSÃO.12 (GND), ADMISSÃO.31 (GND_1), C86.1, C87.1, C94.2, C96.2, C102.2, C122.-, JP2.5, S5.1 (S), S5.2 (S1); also elsewhere on the board
LINHA15: ADMISSÃO.33 (RB0/INT0/FLT0/SRI/AN12); also elsewhere on the board
unnamed: ADMISSÃO.15 (RC0/P2B/T3CKI/T3G/T1CKI/SOSCO), LED16.C
unnamed: LED16.A, R115.1
unnamed: ADMISSÃO.13 (RA7/CLKI/OSC1), C86.2, Q2.1, R174.2
unnamed: ADMISSÃO.1 (~MCLR/VPP/RE3), R113.2
unnamed: C102.1, JP2.1, R113.1, R114.2, S5.3, S5.4 (P1)
unnamed: ADMISSÃO.14 (RA6/CLKO/OSC2), C87.2, Q2.2, R174.1
RA0_ADMISS_TPS_1: ADMISSÃO.2 (RA0/C12IN0-/ANO); also elsewhere on the board
RA1_ADMISS_TPS_2: ADMISSÃO.3 (RA1/C12IN1-/AN1); also elsewhere on the board
RA2_ADMISS_ALTERNADOR: ADMISSÃO.4 (RA2/C2IN+/AN2/DACOUT/VREF-); also elsewhere on the board
RA3_ADMISS_DI2__BORBO: ADMISSÃO.5 (RA3/C1IN+/AN3/VREF+); also elsewhere on the board
RB1_ADMISS_DI1_BORBO: ADMISSÃO.34 (RB1/INT1/C12IN3-/AN10); also elsewhere on the board
RB2_ADMISS_COD_BORBO: ADMISSÃO.35 (RB2/INT32/CTED1/AN8); also elsewhere on the board
RB3_ADMISS_IN1_BORBO: ADMISSÃO.36 (RB3/CTED2/P2A/CCP2/C12IN2-/AN9); also elsewhere on the board
RB4_ADMISS_SF_BORBO: ADMISSÃO.37 (RB4/IOC0/TG5/AN11); also elsewhere on the board
RB5_ADMISS_IN2_BORBO: ADMISSÃO.38 (RB5/IOC1/P3A/CCP3/T3CKI/T1G/AN13); also elsewhere on the board
RB6_ADMISS: ADMISSÃO.39 (RB6/IOC2/PGC), JP2.3
RB7_ADMISS: ADMISSÃO.40 (RB7/IOC3/PGD), JP2.2
RD1_ADMISS_VELOCIDA: ADMISSÃO.20 (RD1/CCP4/SDI2/SDA2/AN21); also elsewhere on the board
RD6_ADMISS_AQUEC_SONDA_1: ADMISSÃO.29 (RD6/P1C/TX2/CK2/AN26); also elsewhere on the board
RD7_ADMISS_AQUEC_SONDA_2: ADMISSÃO.30 (RD7/P1D/RX2/DT2/AN27); also elsewhere on the board
RE1_GERENC_RA5_CHIP_SELEC_ADMISS: ADMISSÃO.7 (RA5/C2OUT/SRNQ/~SS1/HLVDIN/AN4); also elsewhere on the board
RE2_ADMISS_CARVãO: ADMISSÃO.10 (RE2/CCP5/AN7); also elsewhere on the board
SCK1_GERENC: ADMISSÃO.18 (RC3/SCK1/SCL1/AN15); also elsewhere on the board
SDI1_GERENC: ADMISSÃO.24 (RC5/SDO1/AN17); also elsewhere on the board
SDO1_GERENC: ADMISSÃO.23 (RC4/SDI1/SDA1/AN16); also elsewhere on the board

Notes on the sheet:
PIC Admissão
FACULDADE DE TECNOLOGIA DE SANTO ANDRÉ Rua Prefeito Justino Paixão, 150 - Centro Santo André - SP - CEP:09020-130 (11) 4437-2216
MARK 1
